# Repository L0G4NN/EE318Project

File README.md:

# EE318Project

### Setup guide
- Connect the batteries of the vehicle to provide power

- Download the MIT_App_file.aia to your machine.
- Import the file into https://ai2.appinventor.mit.edu/
- Scan the QR on your mobile device
- Connect to the bluetooth device

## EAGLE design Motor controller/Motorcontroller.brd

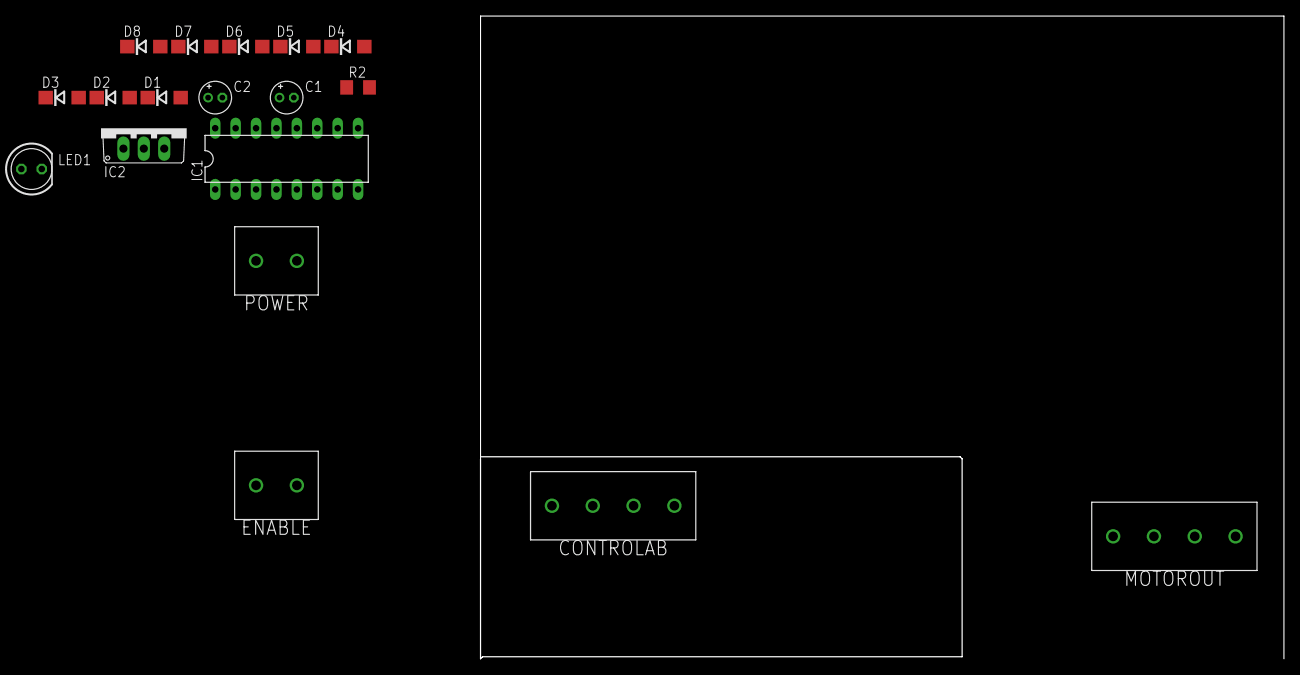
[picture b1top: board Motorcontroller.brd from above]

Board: 2 copper layers, 100.0 x 80.0 mm, 18 parts (0 on the bottom side), 14 nets, no tracks yet.

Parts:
C1, C2: 10u; E1,8-4
CONTROLAB: 2828XX-4282837-4; TERMBLK_508-4N
D1, D2, D3, D4, D5, D6, D7, D8: DO214AC
ENABLE: 2828XX-2282837-2; TERMBLK_508-2N
IC1: L293D; DIL16
IC2: 7805TV; TO220V
LED1: LED5MM
MOTOROUT: 2828XX-4282837-4; TERMBLK_508-4N
POWER: 2828XX-2282837-2; TERMBLK_508-2N
R2: 1k; R1206

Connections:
1-2EN: ENABLE.1, IC1.1
1A: CONTROLAB.1, IC1.2
1Y: D1.A, D5.C, IC1.3, MOTOROUT.1
2A: CONTROLAB.2, IC1.7
2Y: D2.A, D6.C, IC1.6, MOTOROUT.2
3-4EN: ENABLE.2, IC1.9
3A: CONTROLAB.3, IC1.10
3Y: D3.A, D7.C, IC1.11, MOTOROUT.3
4A: CONTROLAB.4, IC1.15
4Y: D4.A, D8.C, IC1.14, MOTOROUT.4
+5V: C1.+, C2.+, D1.C, D2.C, D3.C, D4.C, IC1.8, IC1.16, IC2.1, IC2.3, POWER.1, R2.2
GND: D5.A, D6.A, D7.A, D8.A, IC1.4, IC1.5, IC1.12, IC1.13, POWER.2
unnamed: C1.-, C2.-, IC2.2, LED1.K
unnamed: LED1.A, R2.1

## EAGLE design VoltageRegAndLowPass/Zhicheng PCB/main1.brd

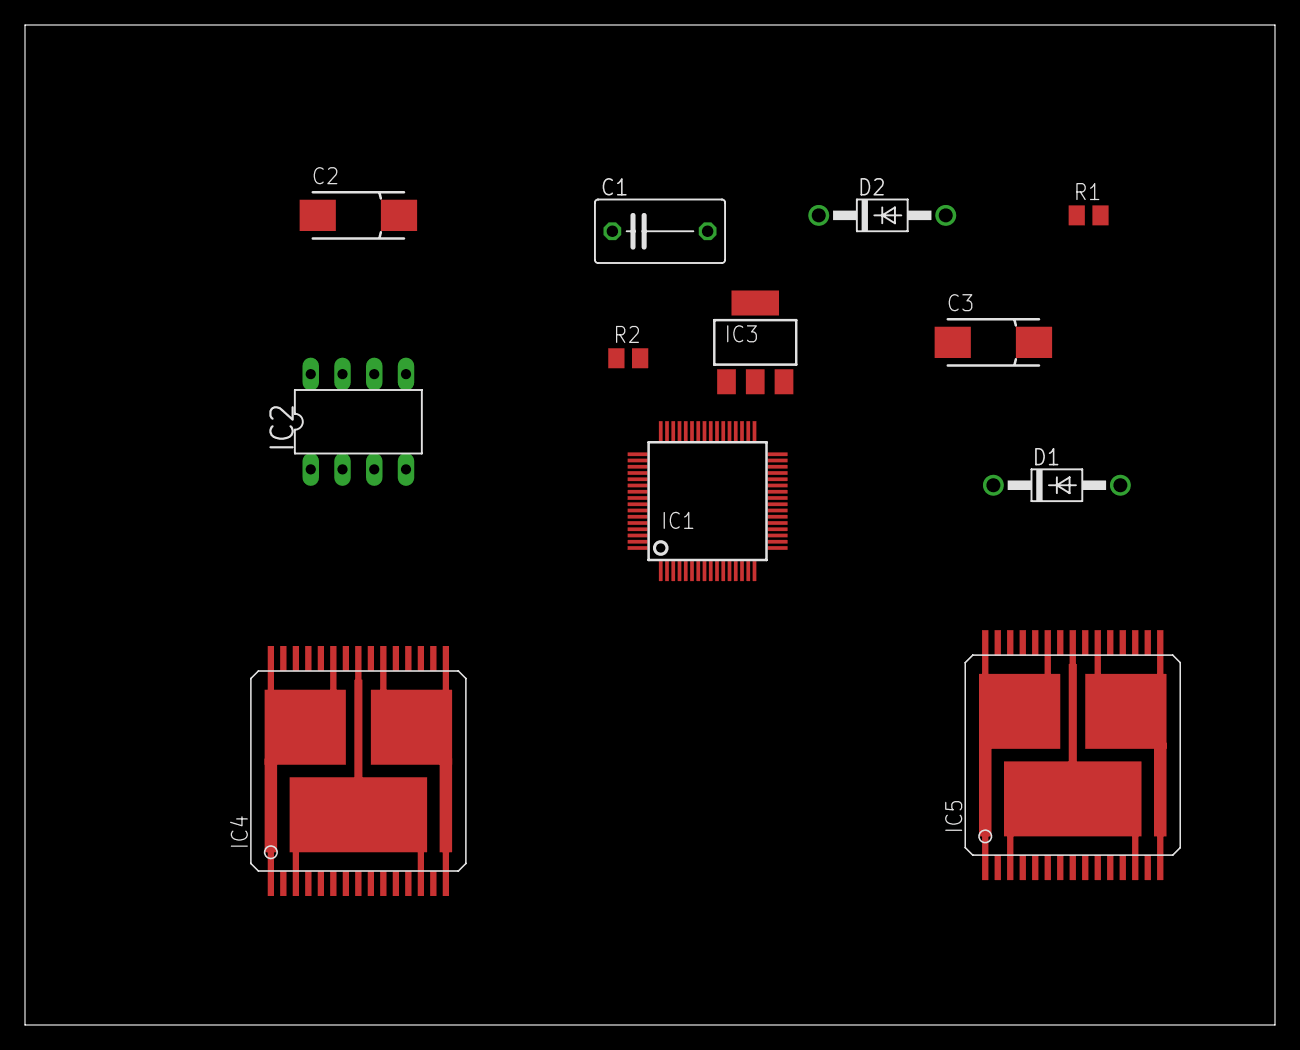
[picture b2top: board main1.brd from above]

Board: 2 copper layers, 100.0 x 80.0 mm, 12 parts (0 on the bottom side), 17 nets, no tracks yet.

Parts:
C1: 0.1uF; C075-052X106
C2: 1uF; 085CS_1AR
C3: 10uF; 085CS_1AR
D1, D2: 1N4002; DO41-10
IC1: MSP430F133; SQFP-S-10X10-64
IC2: HCS410P; DIL8
IC3: LM317MBSTT3; SOT223
IC4, IC5: VNH3SP30; MULTIPOWERSO-30
R1: 240Ω; M0805
R2: 2.1K; M0805

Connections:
0: IC2.5, IC4.26, IC4.27, IC4.28, IC5.26, IC5.27, IC5.28
GND: C1.2, C2.-, C3.-, IC1.62, R2.1
GNDB: IC4.18, IC4.19, IC4.20, IC5.18, IC5.19, IC5.20
unnamed: IC1.36, IC2.8
unnamed: C3.+, D2.A, IC3.1, R1.1, R2.2
unnamed: IC1.38, IC2.1
unnamed: IC1.39, IC2.2
unnamed: IC1.40, IC2.3
unnamed: IC1.28, IC5.11
unnamed: IC1.29, IC5.5
unnamed: IC1.30, IC5.8
unnamed: IC1.12, IC4.11
unnamed: IC1.13, IC4.5
unnamed: IC1.14, IC4.8
VCC: IC4.3, IC4.13, IC4.23, IC4.VCC, IC4.VCC@1, IC5.3, IC5.13, IC5.23, IC5.VCC, IC5.VCC@1
VIN: C1.1, D1.C, IC1.1, IC3.3
VO: C2.+, D1.A, D2.C, IC3.4, R1.2

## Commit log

2024-01-26 template files
2024-01-26 Added motor controller files
2024-01-28 Tested a motor
    tested a motor under a power supply
    roughly took 300mA to power 1 motor
2024-01-31 created BOM
2024-02-01 added protection diodes to circuit
2024-02-01 started coding
2024-02-09 migrated code into composer studio
    https://www.ti.com/tool/CCSTUDIO
    better and easier than IAR - also IAR has licencing issues now
2024-02-09 file struct stuff
2024-02-09 stuff
2024-02-09 think i fixed
2024-02-10 finally fixed how the filesystem works
2024-02-11 some boilerplate code
2024-02-15 small fix
2024-02-15 skeleton outline
2024-02-23 Bit of progress in ISR
2024-02-23 new files
2024-02-28 fixed driverlib
2024-02-29 cleaned workspace
2024-02-29 MEANINGLESS
2024-02-29 motors forward config with LED visualisation
2024-03-03 PWM signals now work using the timers
2024-03-03 comments
2024-03-08 pin change for labtest
2024-03-11 Rollback fix - accidently broke everything
2024-03-14 bluetooth c file
2024-03-14 added useful reference book
2024-03-14 new timer method
2024-03-14 this
2024-03-14 moved daniels file to correct place
2024-03-14 build error fixes
2024-03-14 small push for desktop pc
2024-03-15 fixed
2024-03-15 quick switch
2024-03-15 PWM works
2024-03-16 testing
2024-03-16 playing around
2024-03-17 starting to work
2024-03-18 cant get it working
2024-03-18 motors pretty much work
2024-03-18 why won't it work
2024-03-18 Roll back fix
2024-03-18 finished func
2024-03-19 bluetooth working - ish
2024-03-19 Should run and work
2024-03-19 test
2024-03-19 fixed git error thing
2024-03-19 bluetooth test
2024-03-19 main rollback
2024-03-20 My files seem to have been conflicted
2024-03-21 setting servo
2024-03-22 changes towards actuator - and small bluetooth change
2024-03-25 voltage reg circuit simulations
2024-03-28 Zhicheng PCB files
2024-03-28 motors and acuator smoothing
2024-03-30 servo progress and fixed pwm bugs
2024-04-01 CAILEAN BLUETOOTH
2024-04-02 bug fix
2024-04-22 lab changes
2024-04-28 servo motor - NEEDS TESTING
2024-04-29 very small cleanup
2024-04-30 progression into servo motors
2024-05-01 Servo motor now works
2024-05-01 small fix and file
2024-05-08 final
2024-05-08 deleted files
2024-05-08 added comments for appendices
